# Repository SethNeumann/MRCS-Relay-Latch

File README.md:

# REPO NAME: EagleTemplate-new
## License: Creative Commons Attribution-NonCommercial-ShareAlike

Delete one of the license lines above, and replace this line and following with the contents of the doc.md file

### How to use this template:

  1. Create a repo using this template, 
  2. Use eagle to create your project
  3. Edit the other text files to describe your project
  4. git add .
  5. git commit -m "add to git"
  6. git tag -a 1.0 -m 1.0
  7. git push origin 1.0

This is a template for new eagle designs.
It includes a blank schematic with a title block ready for editing and a
default PCB that uses the SPCoast.lbr's BOARD component, Fiducials and an OSHW logo.

First line: A short description of the project, used as a subtitle or tagline

Remaining lines: a verbose changelog of what makes this "git version" different from the last.
Use this space (in Markdown format) to describe the context and details of the changes.
This section should be 5 to 20 lines of interesting detail; each version tab in the project will 
display this text to help the reader understand why this version is differnet...

The published project on the SPCoast.github.io website will
include the relevant git commit messages as a terse, high level
changelog, so don't replicate those messages here.

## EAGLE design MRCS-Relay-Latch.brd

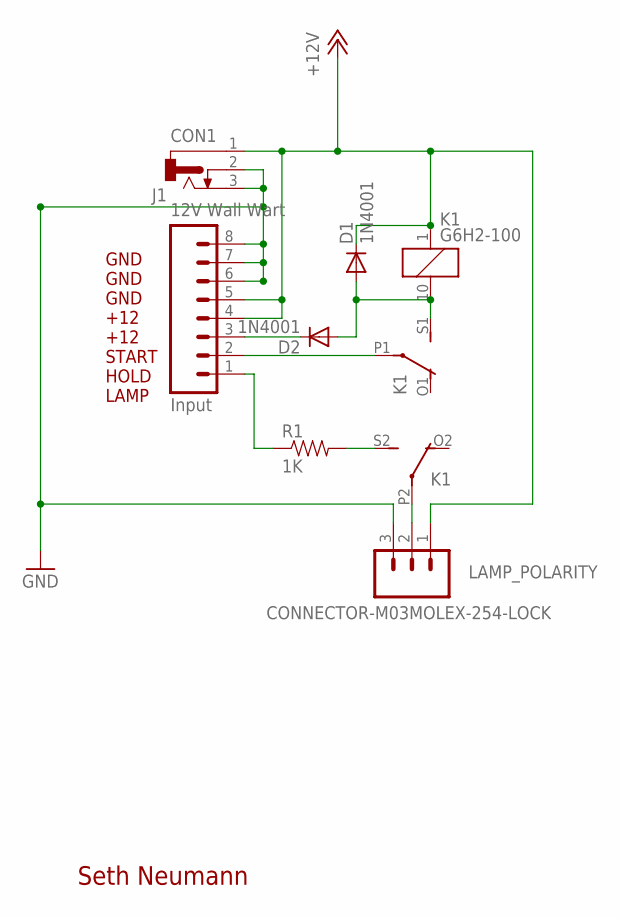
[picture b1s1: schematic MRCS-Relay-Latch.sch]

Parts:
CON1: 12V Wall Wart; DCJ0202
D1, D2: 1N4001; DIODE-1N4001
J1: Input; 1X08_FEMALE_LOCK
K1: G6H2-100
LAMP_POLARITY: CONNECTOR-M03MOLEX-254-LOCK; MOLEX-1X3_LOCK
R1: 1K; AXIAL-0.4-RES

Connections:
+12V: CON1.1, D1.C, J1.4, J1.5, K1.1, LAMP_POLARITY.1
GND: CON1.2, CON1.3, J1.6, J1.7, J1.8, LAMP_POLARITY.3
HOLD: J1.2, K1.P1
LAMP: J1.1, R1.P$1 (1)
unnamed: K1.P2, LAMP_POLARITY.2
unnamed: K1.S2 (S), R1.P$2 (2)
unnamed: D1.A, D2.A, K1.10 (2), K1.S1 (S)
START: D2.C, J1.3

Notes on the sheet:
GND GND GND +12 +12 START HOLD LAMP
Seth Neumann

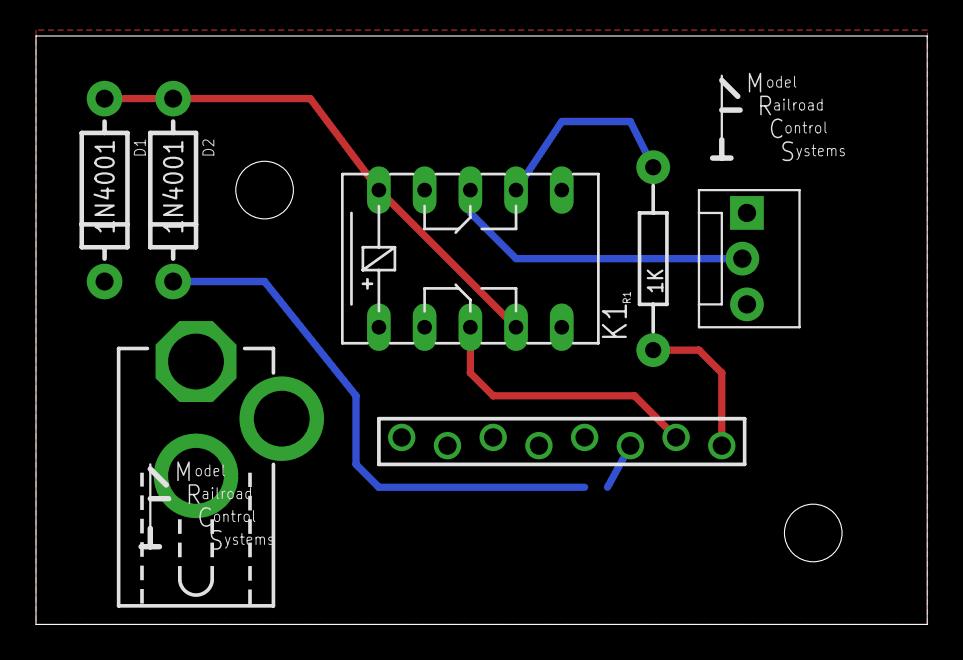
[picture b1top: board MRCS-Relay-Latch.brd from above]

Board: 2 copper layers, 49.5 x 32.7 mm, 11 parts (0 on the bottom side), 8 nets.

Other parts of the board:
U$1: MRCSLOGOBTM
U$2, U$3: MRCSLOGOTOP
U$4: CA-PROP65WARNING

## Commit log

2020-08-04 Update DESCRIPTION
    Lighting an indicator (a limiting resistor is provided for LEDs, but a 12V light bulb can be substituted) after a station is initially called (buzzed): the indicator will remain lit until the associa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
    Lighting an indicator at the Dispatcher’s desk indicating that a call request has been made but not answered
    Features:
    12 VDC operation
    Option of on-board power from a wall wart via 2.1mm plug or screw terminals for use with 12V layout auxiliary power bus.
    Lat
2020-08-04 Update INFO
2020-08-04 add to git
2020-08-04 Update DESCRIPTION
